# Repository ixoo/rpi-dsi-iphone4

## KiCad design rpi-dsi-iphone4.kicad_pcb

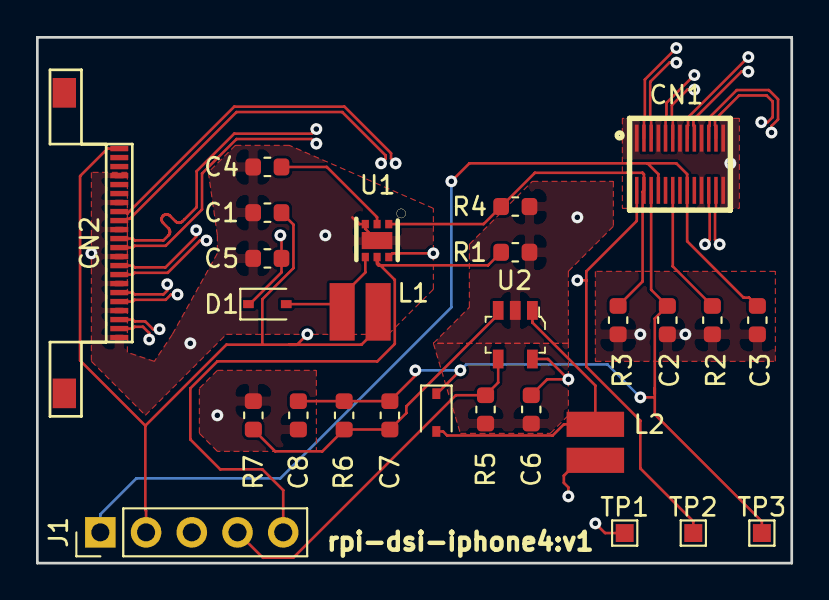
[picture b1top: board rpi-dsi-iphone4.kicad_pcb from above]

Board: 4 copper layers, 41.9 x 29.2 mm, 27 parts (0 on the bottom side), 23 nets.

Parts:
C1, C5, C8: 1uF; C_0603_1608Metric
C2, C3: 100nF; C_0603_1608Metric
C4: 220nF; C_0603_1608Metric
C6: 4.7uF; C_0603_1608Metric
C7: 22pF; C_0603_1608Metric
CN1: iP4; IPHONE4_LCD_CONN
CN2: Molex 54548-2271; FPC_22
D1, D2: BAS170W; D_SOD-323
J1: Conn_01x05_Male; PinHeader_1x05_P2.54mm_Vertical
L1: 22uH; IND_PANASONIC_ELLVEG
L2: 4.7uH; IND_PANASONIC_ELLVEG
R1, R5, R6: 100k; R_0603_1608Metric
R2: 3k3; R_0603_1608Metric
R3, R4: 10; R_0603_1608Metric
R7: 27k; R_0603_1608Metric
TP1, TP2, TP3: TestPoint; TestPoint_Pad_1.0x1.0mm
U1: LV52204; UDFN6_2X2_065P
U2: TPS61040DBVR; SOT-753

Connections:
+1V8: C3.1, CN1.8, CN1.16, J1.1
+3V3: C1.1, C6.1, CN2.1, J1.2, L1.1, L2.1, U1.6, U2.5
/DSI_RESET_N: CN1.12, R2.2
BL_DIM: J1.5, R1.1, U1.5
DSI_CLK_N: CN1.17, CN2.15
DSI_CLK_P: CN1.15, CN2.14
DSI_L0_N: CN1.3, CN2.21
DSI_L0_P: CN1.5, CN2.20
DSI_L1_N: CN1.11, CN2.18
DSI_L1_P: CN1.9, CN2.17
DSI_L2_N: CN1.21, CN2.12
DSI_L2_P: CN1.23, CN2.11
DSI_L3_N: CN1.24, CN2.9
DSI_L3_P: CN1.22, CN2.8
GND: C1.2, C2.2, C3.2, C4.2, C5.2, C6.2, C8.2, CN1.1, CN1.7, CN1.13, CN1.19, CN1.20, CN1.25, CN1.26, CN2.4, CN2.7, CN2.10, CN2.13, CN2.16, CN2.19, CN2.22, J1.3, R1.2, R2.1, R3.2, R4.2, R5.2, R7.1, TP1.1, U1.3, U1.7, U2.2
LCD_BL_A: C5.1, CN1.2, D1.1, TP2.1
LCD_BL_FB: CN1.4, R3.1, R4.1, U1.1
LCD_PVDD: C2.1, C7.1, C8.1, CN1.6, D2.1, R6.1, TP3.1
LCD_PWREN: J1.4, R5.1, U2.4
unnamed: C4.1, U1.2
unnamed: C7.2, R6.2, R7.2, U2.3
unnamed: D1.2, L1.2, U1.4
unnamed: D2.2, L2.2, U2.1

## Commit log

2018-08-16 First revision of the board.
    All SMD on one side.
    DSI differential pairs adjusted for length and pair phase skew.
    Test points to validate generated voltage for LCD Bias and LED backlight.
